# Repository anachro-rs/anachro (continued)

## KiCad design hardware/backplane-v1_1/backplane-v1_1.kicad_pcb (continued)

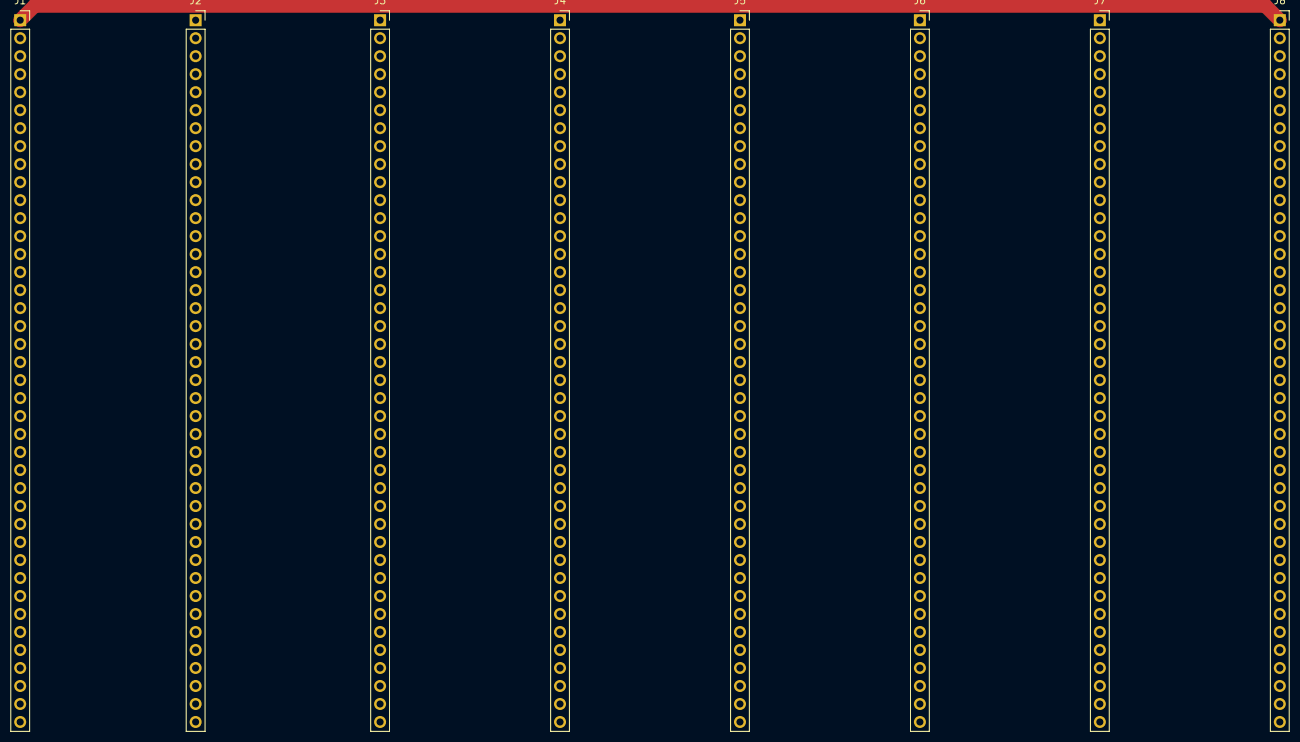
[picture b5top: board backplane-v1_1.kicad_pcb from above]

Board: 2 copper layers, 8 parts (0 on the bottom side), 40 nets.

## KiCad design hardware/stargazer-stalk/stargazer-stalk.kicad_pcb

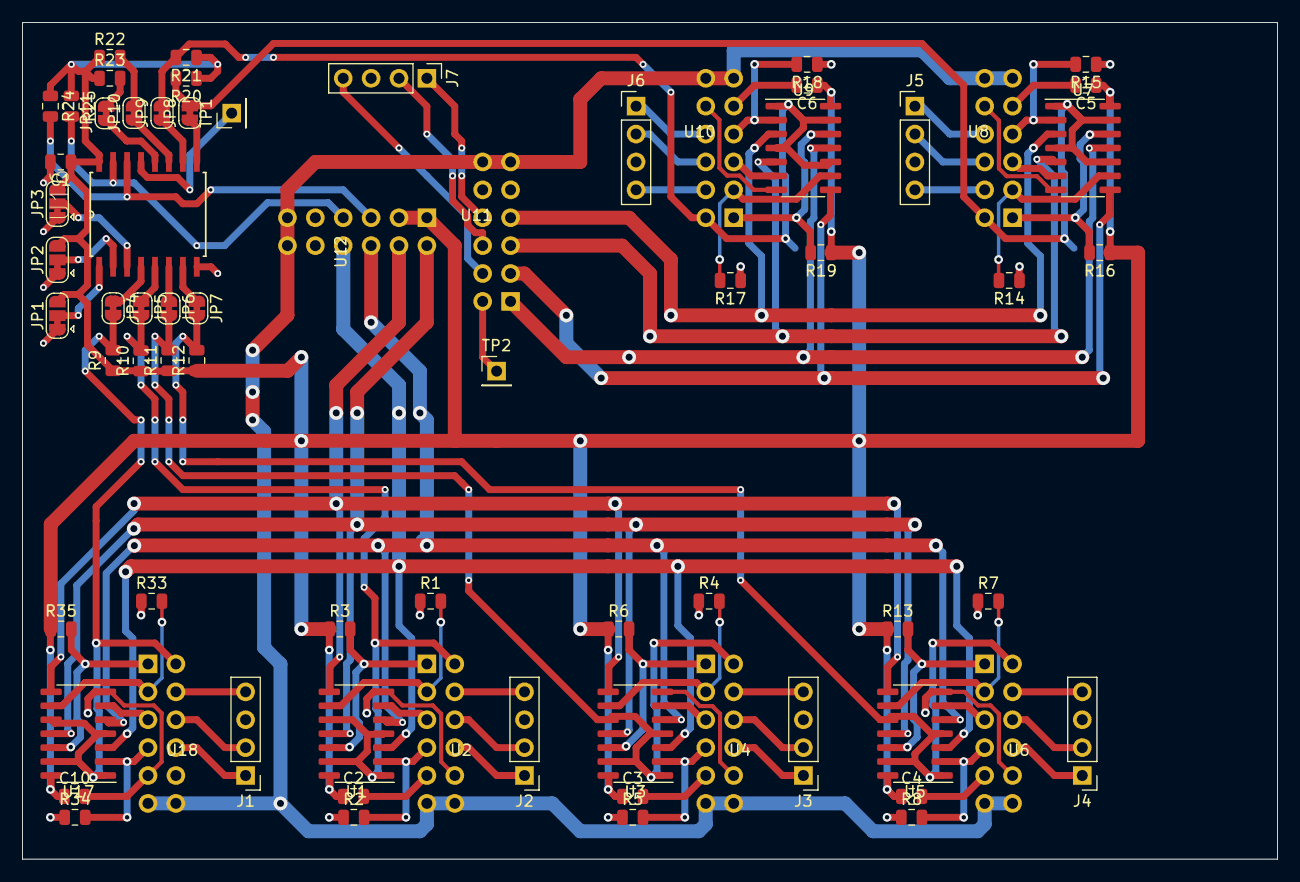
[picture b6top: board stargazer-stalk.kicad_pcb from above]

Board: 2 copper layers, 114.3 x 76.2 mm, 70 parts (0 on the bottom side), 79 nets.

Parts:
C1, C2, C3, C4, C5, C6, C10: 0.1uF; C_0805_2012Metric
J1, J2, J3, J4, J5, J6, J7: swd-basic; PinHeader_1x04_P2.54mm_Vertical
JP1, JP2, JP3: SolderJumper_3_Bridged12; SolderJumper-3_P1.3mm_Bridged12_RoundedPad1.0x1.5mm
JP4, JP5, JP6, JP7, JP8, JP9, JP10, JP11: SolderJumper_2_Bridged; SolderJumper-2_P1.3mm_Bridged_RoundedPad1.0x1.5mm
R1, R2, R3, R4, R5, R6, R7, R8, R13, R14, R15, R16, R17, R18, R19, R33, R34, R35: 100k; R_0805_2012Metric
R9, R10, R11, R12, R20, R21, R22, R23: 10k; R_0805_2012Metric
R24, R25: R; R_0805_2012Metric
TP1, TP2: TestPoint; PinHeader_1x01_P2.54mm_Vertical
U1, U3, U5, U7, U9, U17: SN74LVC125AD; SOIC-14_3.9x8.7mm_P1.27mm
U2, U4, U6, U8, U10, U18: pmod-interface-type-2a; pmod-double-vertical
U11: pmod-interface-type-2a-arb; pmod-double-vertical
U12: pmod-interface-type-6a-arb; pmod-double-vertical
U16: PCF8574; SOIC127P1032X265-16N

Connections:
+3V3: C1.1, C2.1, C3.1, C4.1, C5.1, C6.1, C10.1, JP1.3, JP2.3, JP3.3, R3.1, R6.1, R9.1, R10.1, R11.1, R12.1, R13.1, R16.1, R19.1, R20.1, R21.1, R22.1, R23.1, R24.1, R25.1, R35.1, U1.14, U3.14, U5.14, U7.14, U9.14, U12.1, U12.2, U16.16, U17.14
+5V: U2.6, U2.12, U4.6, U4.12, U6.6, U6.12, U8.6, U8.12, U10.6, U10.12, U11.6, U11.12, U12.6, U12.12, U18.6, U18.12
/ADDR0: JP1.2, U16.1
/ADDR1: JP2.2, U16.2
/ADDR2: JP3.2, U16.3
/CIPOx: U7.5, U9.5, U11.3
/COPIx: U7.8, U9.8, U11.2
/CSnx: U7.11, U9.11, U11.1
/GO1: JP4.2, R9.2, U17.1, U17.4, U17.10, U17.13, U18.7
/GO2: JP5.2, R10.2, U1.1, U1.4, U1.10, U1.13, U2.7
/GO3: JP6.2, R11.2, U3.1, U3.4, U3.10, U3.13, U4.7
/GO4: JP7.2, R12.2, U5.1, U5.4, U5.10, U5.13, U6.7
/GO5: JP8.2, R20.2, U7.1, U7.4, U7.10, U7.13, U8.7
/GO6: JP9.2, R21.2, U9.1, U9.4, U9.10, U9.13, U10.7
/GO7: JP10.2, R22.2
/GO8: JP11.2, R23.2
/MISC-ARB: TP2.1, U11.7
/OPT-CIPOx: U1.5, U3.5, U5.5, U12.9, U17.5
/OPT-COPIx: U1.8, U3.8, U5.8, U12.8, U17.8
/OPT-CSnx: U1.11, U3.11, U5.11, U12.7, U17.11
/OPT-SCKx: U1.3, U3.3, U5.3, U12.10, U17.3
/PORT-SCL: R24.2, U12.3, U16.14
/PORT-SDA: R25.2, U12.4, U16.15
/RST-ARB: J7.4, U11.8
/SCKx: U7.3, U9.3, U11.4
/SWCLK-ARB: J7.1, U11.10
/SWDIO-ARB: J7.2, U11.9
/card-1/CIPO: U17.6, U18.3
/card-1/COPI: R33.2, U17.9, U18.2
/card-1/CSn: R35.2, U17.12, U18.1
/card-1/RST: J1.4, U18.8
/card-1/SCK: R34.2, U17.2, U18.4
/card-1/SWCLK: J1.1, U18.10
/card-1/SWDIO: J1.2, U18.9
/card-2/CIPO: U1.6, U2.3
/card-2/COPI: R1.2, U1.9, U2.2
/card-2/CSn: R3.2, U1.12, U2.1
/card-2/RST: J2.4, U2.8
/card-2/SCK: R2.2, U1.2, U2.4
/card-2/SWCLK: J2.1, U2.10
/card-2/SWDIO: J2.2, U2.9
/card-3/CIPO: U3.6, U4.3
/card-3/COPI: R4.2, U3.9, U4.2
/card-3/CSn: R6.2, U3.12, U4.1
/card-3/RST: J3.4, U4.8
/card-3/SCK: R5.2, U3.2, U4.4
/card-3/SWCLK: J3.1, U4.10
/card-3/SWDIO: J3.2, U4.9
/card-4/CIPO: U5.6, U6.3
/card-4/COPI: R7.2, U5.9, U6.2
/card-4/CSn: R13.2, U5.12, U6.1
/card-4/RST: J4.4, U6.8
/card-4/SCK: R8.2, U5.2, U6.4
/card-4/SWCLK: J4.1, U6.10
/card-4/SWDIO: J4.2, U6.9
/card-5/CIPO: U7.6, U8.3
/card-5/COPI: R14.2, U7.9, U8.2
/card-5/CSn: R16.2, U7.12, U8.1
/card-5/RST: J5.4, U8.8
/card-5/SCK: R15.2, U7.2, U8.4
/card-5/SWCLK: J5.1, U8.10
/card-5/SWDIO: J5.2, U8.9
/card-6/CIPO: U9.6, U10.3
/card-6/COPI: R17.2, U9.9, U10.2
/card-6/CSn: R19.2, U9.12, U10.1
/card-6/RST: J6.4, U10.8
/card-6/SCK: R18.2, U9.2, U10.4
/card-6/SWCLK: J6.1, U10.10
/card-6/SWDIO: J6.2, U10.9
GND: C1.2, C2.2, C3.2, C4.2, C5.2, C6.2, C10.2, J1.3, J2.3, J3.3, J4.3, J5.3, J6.3, J7.3, JP1.1, JP2.1, JP3.1, R1.1, R2.1, R4.1, R5.1, R7.1, R8.1, R14.1, R15.1, R17.1, R18.1, R33.1, R34.1, U1.7, U2.5, U2.11, U3.7, U4.5, U4.11, U5.7, U6.5, U6.11, U7.7, U8.5, U8.11, U9.7, U10.5, U10.11, U11.5, U11.11, U12.5, U12.11, U16.8, U17.7, U18.5, U18.11
unnamed: JP4.1, U16.4
unnamed: JP5.1, U16.5
unnamed: JP6.1, U16.6
unnamed: JP7.1, U16.7
unnamed: JP8.1, U16.9
unnamed: JP9.1, U16.10
unnamed: JP10.1, U16.11
unnamed: JP11.1, U16.12
unnamed: TP1.1, U16.13

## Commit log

2020-08-04 Working server connection, no logic
2020-08-04 Minimal pubsub
2020-08-14 Totally rework to a better data layout
2020-08-14 Better path matching
2020-08-14 Split into server and connection manager
2020-08-15 huge matches
2020-08-15 Wrangle lifetimes
2020-08-15 Seems to mostly work!
2020-08-15 Make version not a string
2020-08-16 icd and client are no-std
2020-08-16 handle no_std icd in server
2020-08-16 Server no_std
2020-08-16 Fully no-std server
2020-08-16 Fix sending logic, working no std client and server
2020-08-17 Fix sub
2020-08-23 Fixup ICD
2020-08-23 Pre-release
2020-08-23 Update docs
2020-08-23 Move licenses up
2020-08-23 Add top level readme
2020-08-26 Add receive macro
2020-08-30 Yesterday work
2020-08-30 UUUUUUGH LIFETIMES
2020-08-30 Roll back a bit
2020-08-31 Lifetimes seem to work?
2020-08-31 Macros fought!
2020-08-31 Working
2020-09-01 Clippy and fmt fixes
2020-09-01 Appears to work!
2020-09-02 anachro-icd v0.1.2 release
2020-09-02 Clean up and reorganize
2020-09-02 No magic numbers!
2020-09-02 Even less magic!
2020-09-02 Docs cleanup
2020-09-02 Cargo fmt
2020-09-02 Pre release clean up
2020-09-02 Ready for release
2020-09-02 Fix demos
2020-09-16 Re-organize
2020-09-19 Trait interfaces for SPI LL and HL
2020-09-19 Start working on PC examples
2020-09-19 Implement SPI Arbitrator TCP sim
2020-09-19 Working LL Arb and Comp
2020-09-19 Implement high level interface for arbitrator
2020-09-20 Working Component and Arbitrator!
2020-09-20 Start work and cargo fmt
2020-09-20 Move arbitrator over to bbqueue
2020-09-20 Move Component to bbqueue
2020-09-20 Move logic to SPI crate
2020-09-20 Move Component logic into SPI crate
2020-09-20 End of stream
2020-09-26 Lifetimes conquered for now
2020-09-26 Realizing I need to re-architect the broker a bit
2020-09-26 Sort of working, lots of bad error handling and errors
2020-09-27 Working pretty well!
2020-09-27 A little cleanup
2020-09-27 Clean up spi crates
2020-09-28 Working on spi support
2020-09-28 Use vendored nrf52
2020-09-28 Update nrf52
2020-09-28 Add spi test template
2020-09-29 Loopback testing
2020-09-30 Compiling example, doesn't work, adding defmt
2020-10-01 Adding defmt
    Starting to make sense, it seems like my csn logic isn't really good enough, because
    we need the line to come full low to finish each transaction.
2020-10-01 Add empty groundhog
2020-10-02 0.1.0 release of groundhog
2020-10-02 pre-rework
2020-10-03 Rework SPI Component
2020-10-03 Updated spi arbitrator
2020-10-03 Updated spi-nrf52
2020-10-06 Connection works
2020-10-06 Update submodules
2020-10-07 OH NOW IT WORKS
2020-10-07 Add embedded projects
2020-10-07 rtic fleet uarte works
2020-10-07 Sort of works? But crashes immediately
2020-10-07 WERKZ
2020-10-07 Arbitrator updated to process both ports
2020-10-07 Fix defmt timer usage
2020-10-07 Make CPU a bit more reliable
2020-10-07 We read keypresses!
2020-10-08 Start working on rpi
2020-10-08 Basic working example
2020-10-08 Demo!
2020-10-10 Initial blank docs
2020-10-10 Fix publish path
2020-10-10 First pass
2020-10-10 Add stargazer docs
2020-10-10 Mention docs in the readme
2020-10-11 Docs work
2020-10-11 Add arbitrator spreadsheet embed
2020-10-12 Schematic capture!
2020-10-12 Some basic routing
2020-10-12 HTTPS submodule
2020-10-12 Now with thicc spaghetti
2020-10-13 Pare down empty docs
2020-10-13 Work on the stalk, currently in MIR mode
2020-10-13 Working before reworking to a 4 card system
2020-10-14 Finished routing, but it's probably too much for 2 layers
2020-10-14 Add links
2020-10-16 Add feather card
2020-11-08 I dunno. working on v2 of the rack
2020-11-09 Anachro test rack v2, plus fixed level shifter
2020-12-02 groundhog-nrf52 publish
2020-12-02 0.2.0
2020-12-02 Adding nrf52840 usage example to groundhog-nrf52
    This PR adds a basic usage rustdoc block that shows how to combine
    the timer together with RTIC.
2020-12-02 0.2.1
2021-03-16 Add initialize check
2021-03-16 Add twim driver with timeout
2021-03-17 Add delay impls
2022-07-04 docs/intro: change link to RustLab 2020 to point to their archive
    The original is gone and not loading on archive.org.
